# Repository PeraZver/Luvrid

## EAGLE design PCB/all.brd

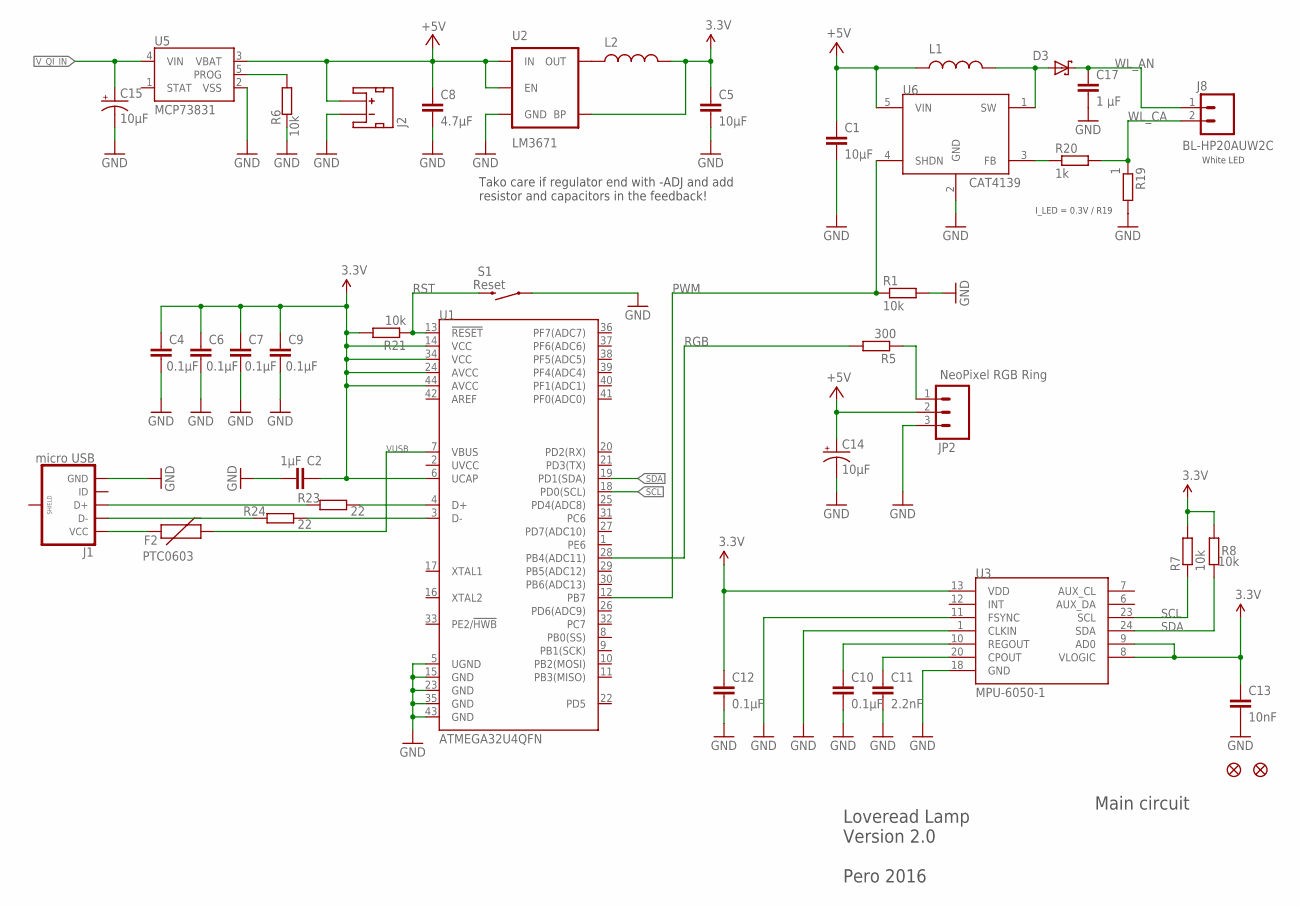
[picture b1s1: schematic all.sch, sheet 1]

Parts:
C1, C5: 10μF; C0603K
C2: 1µF; C0603
C4, C6, C7, C9, C10, C12: 0.1μF; C0603K
C8: 4.7μF; C0603K
C11: 2.2nF; C0603K
C13: 10nF; C0603K
C14, C15: 10μF; EIA3216
C17: 1 μF; C0603K
D3: SMF5.0AT1; SOD123FL
F2: PTC0603; 0603
FD1, FD2: FIDUCIAL1X2; FIDUCIAL-1X2
J1: micro USB; USB-B-MICRO-SMD_V03
J2: LIPO-BATTERY-CONNECTOR; JST-LIPO-CONNECTOR-1.25MM
J8: BL-HP20AUW2C; 1X02
JP2: NeoPixel RGB Ring; 1X03
L1: 22uH; SDR0403
L2: 2.2uH; SDR0403
R1, R6, R7, R8, R21: 10k; R0603
R5: 300; R0603
R19: 1; R0603
R20: 1k; R0603
R23, R24: 22; R0603
S1: Reset; TACTILE-SWITCH-SKSGAAE010
U1: ATMEGA32U4QFN; QFN-44
U2: LM3671; SOT23-5
U3: MPU-6050-1; QFN-24-4MM2
U5: MCP73831; SOT23-5
U6: CAT4139; SOT23-5

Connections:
3.3V: C2.1, C4.1, C5.1, C6.1, C7.1, C9.1, C12.1, C13.1, L2.P$2 (2), R7.2, R8.2, R21.2, U1.6 (UCAP), U1.14 (VCC), U1.24 (AVCC), U1.34 (VCC), U1.44 (AVCC), U2.4 (BP), U3.8 (VLOGIC), U3.9 (AD0), U3.13 (VDD)
+5V: C1.1, C8.1, C14.A (+), J2.P$1 (+), JP2.2, L1.P$1 (1), U2.1 (IN), U2.3 (EN), U5.3 (VBAT), U6.5 (VIN)
GND: C1.2, C2.2, C4.2, C5.2, C6.2, C7.2, C8.2, C9.2, C10.2, C11.2, C12.2, C13.2, C14.C (-), C15.C (-), C17.2, J1.GND, J2.P$2 (-), JP2.3, R1.2, R6.1, R19.2, S1.P$1 (1), S1.P$3 (1), U1.5 (UGND), U1.15 (GND), U1.23 (GND), U1.35 (GND), U1.43 (GND), U2.2 (GND), U3.1 (CLKIN), U3.11 (FSYNC), U3.18 (GND), U5.2 (VSS), U6.2 (GND); also elsewhere on the board
unnamed: C11.1, U3.20 (CPOUT)
unnamed: C10.1, U3.10 (REGOUT)
unnamed: JP2.1, R5.1
unnamed: R6.2, U5.5 (PROG)
unnamed: D3.A, L1.P$2 (2), U6.1 (SW)
unnamed: R20.1, U6.3 (FB)
unnamed: L2.P$1 (1), U2.5 (OUT)
unnamed: F2.1, J1.VBUS (VCC)
unnamed: J1.D+, R23.1
unnamed: J1.D-, R24.1
unnamed: R23.2, U1.4 (D+)
unnamed: R24.2, U1.3 (D-)
PWM: R1.1, U1.12 (PB7), U6.4 (SHDN)
RGB: R5.2, U1.28 (PB4(ADC11))
RST: R21.1, S1.P$2 (2), S1.P$4 (2), U1.13 (!RESET)
SCL: R7.1, U1.18 (PD0(SCL)), U3.23 (SCL)
SDA: R8.1, U1.19 (PD1(SDA)), U3.24 (SDA)
VUSB: F2.2, U1.7 (VBUS)
V_QI_IN: C15.A (+), U5.4 (VIN); also elsewhere on the board
WL_AN: C17.1, D3.C, J8.1
WL_CA: J8.2, R19.1, R20.2

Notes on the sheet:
Loveread Lamp Version 2.0 Pero 2016
Main circuit
I_LED = 0.3V / R19
White LED
Tako care if regulator end with -ADJ and add resistor and capacitors in the feedback!

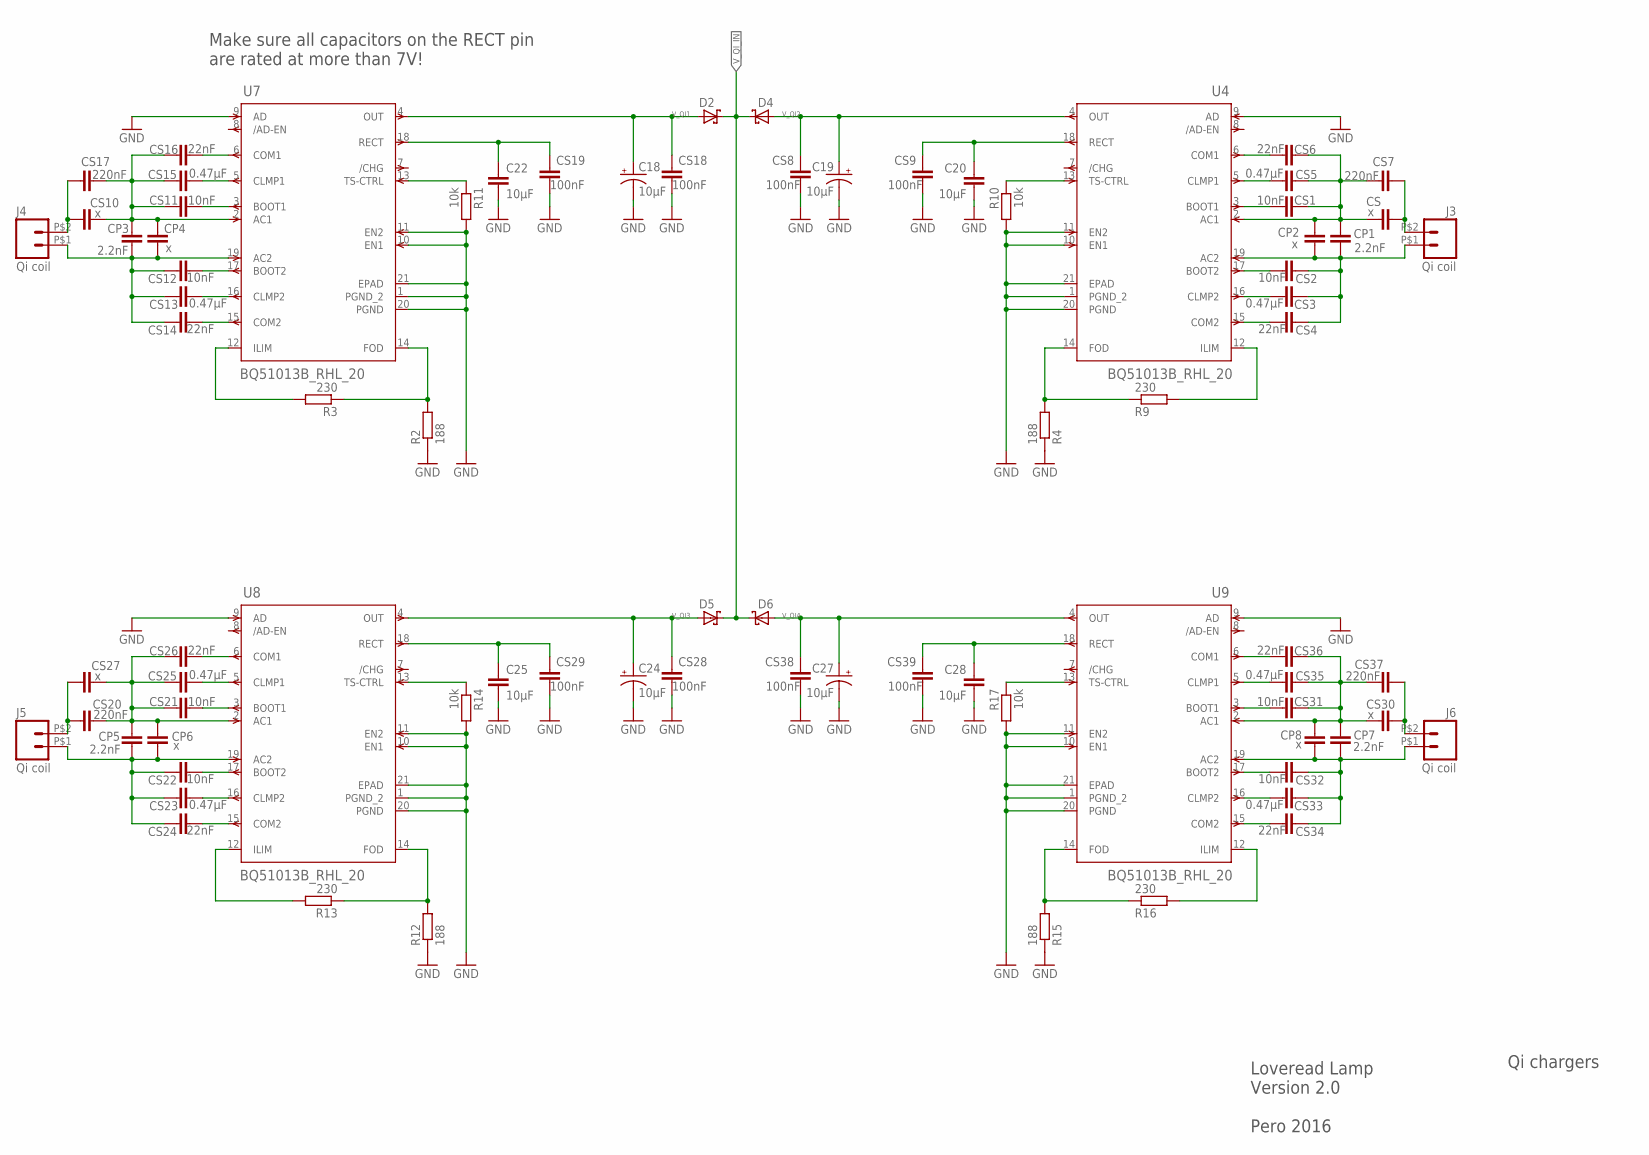
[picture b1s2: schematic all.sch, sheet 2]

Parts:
C18, C19, C24, C27: 10μF; EIA3216
C20, C22, C25, C28: 10μF; C0603K
CP1, CP3, CP5, CP7: 2.2nF; C0603K
CP2, CP4, CP6, CP8: x; C0603K
CS, CS10, CS27, CS30: x; C0603K
CS1, CS2, CS11, CS12, CS21, CS22, CS31, CS32: 10nF; C0603K
CS3, CS5, CS13, CS15, CS23, CS25, CS33, CS35: 0.47μF; C0603K
CS4, CS6, CS14, CS16, CS24, CS26, CS34, CS36: 22nF; C0603K
CS7, CS17, CS20, CS37: 220nF; C0603K
CS8, CS9, CS19, CS28, CS29, CS38, CS39: 100nF; C0603K
CS18: 100nF; C0603
D2, D4, D5, D6: SMF5.0AT1; SOD123FL
J3, J4, J5, J6: Qi coil; 1X02_BIG
R2, R4, R12, R15: 188; R0603
R3, R9, R13, R16: 230; R0603
R10, R11, R14, R17: 10k; R0603
U4, U7, U8, U9: BQ51013B_RHL_20; RHL20_2P05X3P05

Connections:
GND: C18.C (-), C19.C (-), C20.2, C22.2, C24.C (-), C25.2, C27.C (-), C28.2, CS8.2, CS9.2, CS18.2, CS19.2, CS28.2, CS29.2, CS38.2, CS39.2, R2.1, R4.1, R10.2, R11.2, R12.1, R14.2, R15.1, R17.2, U4.1 (PGND_2), U4.9 (AD), U4.10 (EN1), U4.11 (EN2), U4.20 (PGND), U4.21 (EPAD), U7.1 (PGND_2), U7.9 (AD), U7.10 (EN1), U7.11 (EN2), U7.20 (PGND), U7.21 (EPAD), U8.1 (PGND_2), U8.9 (AD), U8.10 (EN1), U8.11 (EN2), U8.20 (PGND), U8.21 (EPAD), U9.1 (PGND_2), U9.9 (AD), U9.10 (EN1), U9.11 (EN2), U9.20 (PGND), U9.21 (EPAD); also elsewhere on the board
unnamed: CS10.1, CS17.1, J4.P$2 (2)
unnamed: CP3.1, CP4.1, CS12.1, CS13.1, CS14.1, J4.P$1 (1), U7.19 (AC2)
unnamed: CP1.2, CP2.2, CS.2, CS1.1, CS5.1, CS6.1, CS7.2, U4.2 (AC1)
unnamed: CS.1, CS7.1, J3.P$2 (2)
unnamed: CP1.1, CP2.1, CS2.1, CS3.1, CS4.1, J3.P$1 (1), U4.19 (AC2)
unnamed: CS1.2, U4.3 (BOOT1)
unnamed: CS2.2, U4.17 (BOOT2)
unnamed: CS3.2, U4.16 (CLMP2)
unnamed: CS11.2, U7.3 (BOOT1)
unnamed: CS4.2, U4.15 (COM2)
unnamed: CS6.2, U4.6 (COM1)
unnamed: CS5.2, U4.5 (CLMP1)
unnamed: CS12.2, U7.17 (BOOT2)
unnamed: C20.1, CS9.1, U4.18 (RECT)
unnamed: R9.2, U4.12 (ILIM)
unnamed: R4.2, R9.1, U4.14 (FOD)
unnamed: R10.1, U4.13 (TS-CTRL)
unnamed: CS13.2, U7.16 (CLMP2)
unnamed: CS14.2, U7.15 (COM2)
unnamed: CS16.2, U7.6 (COM1)
unnamed: CS15.2, U7.5 (CLMP1)
unnamed: CP3.2, CP4.2, CS10.2, CS11.1, CS15.1, CS16.1, CS17.2, U7.2 (AC1)
unnamed: C22.1, CS19.1, U7.18 (RECT)
unnamed: R3.2, U7.12 (ILIM)
unnamed: R2.2, R3.1, U7.14 (FOD)
unnamed: R11.1, U7.13 (TS-CTRL)
unnamed: CS20.1, CS27.1, J5.P$2 (2)
unnamed: CP5.1, CP6.1, CS22.1, CS23.1, CS24.1, J5.P$1 (1), U8.19 (AC2)
unnamed: CS21.2, U8.3 (BOOT1)
unnamed: CS22.2, U8.17 (BOOT2)
unnamed: CS23.2, U8.16 (CLMP2)
unnamed: CS24.2, U8.15 (COM2)
unnamed: CS26.2, U8.6 (COM1)
unnamed: CS25.2, U8.5 (CLMP1)
unnamed: CP5.2, CP6.2, CS20.2, CS21.1, CS25.1, CS26.1, CS27.2, U8.2 (AC1)
unnamed: C25.1, CS29.1, U8.18 (RECT)
unnamed: R13.2, U8.12 (ILIM)
unnamed: R12.2, R13.1, U8.14 (FOD)
unnamed: R14.1, U8.13 (TS-CTRL)
unnamed: CS30.1, CS37.1, J6.P$2 (2)
unnamed: CP7.1, CP8.1, CS32.1, CS33.1, CS34.1, J6.P$1 (1), U9.19 (AC2)
unnamed: CS31.2, U9.3 (BOOT1)
unnamed: CS32.2, U9.17 (BOOT2)
unnamed: CS33.2, U9.16 (CLMP2)
unnamed: CS34.2, U9.15 (COM2)
unnamed: CS36.2, U9.6 (COM1)
unnamed: CS35.2, U9.5 (CLMP1)
unnamed: CP7.2, CP8.2, CS30.2, CS31.1, CS35.1, CS36.1, CS37.2, U9.2 (AC1)
unnamed: C28.1, CS39.1, U9.18 (RECT)
unnamed: R16.2, U9.12 (ILIM)
unnamed: R15.2, R16.1, U9.14 (FOD)
unnamed: R17.1, U9.13 (TS-CTRL)
V_QI1: C18.A (+), CS18.1, D2.A, U7.4 (OUT)
V_QI2: C19.A (+), CS8.1, D4.A, U4.4 (OUT)
V_QI3: C24.A (+), CS28.1, D5.A, U8.4 (OUT)
V_QI4: C27.A (+), CS38.1, D6.A, U9.4 (OUT)
V_QI_IN: D2.C, D4.C, D5.C, D6.C; also elsewhere on the board

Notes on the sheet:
Loveread Lamp Version 2.0 Pero 2016
Qi chargers
Make sure all capacitors on the RECT pin are rated at more than 7V!

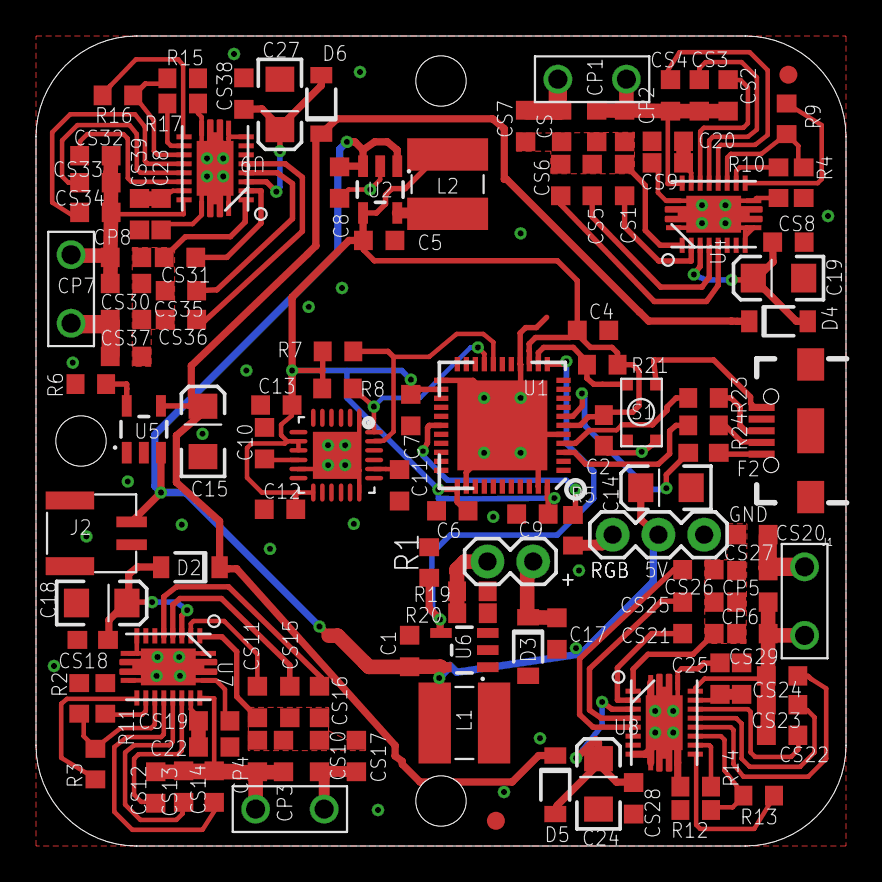
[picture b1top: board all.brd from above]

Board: 2 copper layers, 45.0 x 45.0 mm, 123 parts (0 on the bottom side), 80 nets.

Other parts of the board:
DRILEGEND: DRILEGEND
U$1: Loveread Lamp v2.0; A4L-LOC

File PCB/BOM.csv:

"Qty";"Value";"Device";"Package";"Parts";"Description";"DATASHEETURL";"DESCRIPTION";"DIST";"DIST_ID";"FAMILY_NAME";"GENERIC_PART_NUMBER";"INDUSTRY_STD_PKG_TYPE";"MANUFACTURER";"MANUFACTURER_PART_NUMBER";"PACKAGE_DESIGNATOR";"PIN_COUNT";"PROD_ID";"RS-NUMBER";"SUPPLIER-ID";"VALUE";"VENDOR";
"2";"";"JUMPER-PAD-3-2OF3_NC_BY_TRACE_SMALL";"PAD-JUMPER-3-2OF3_NC_BY_TRACE_YES_SILK_FULL_BOX";"SJ1, SJ2";"";"";"";"";"";"";"";"";"";"";"";"";"";"";"";"";"";
"5";"0.1µF";"C-EUC0603K";"C0603K";"C6, C7, C9, C10, C12";"CAPACITOR, European symbol";"";"";"";"";"";"";"";"";"";"";"";"";"";"";"";"";
"8";"0.47µF";"C-EUC0603K";"C0603K";"CS3, CS5, CS13, CS15, CS23, CS25, CS33, CS35";"CAPACITOR, European symbol";"";"";"";"";"";"";"";"";"";"";"";"";"";"";"";"";
"1";"1";"R-EU_R0603";"R0603";"R19";"RESISTOR, European symbol";"";"";"";"";"";"";"";"";"";"";"";"";"";"";"";"";
"1";"1 µF";"C-EUC0603K";"C0603K";"C17";"CAPACITOR, European symbol";"";"";"";"";"";"";"";"";"";"";"";"";"";"";"";"";
"1";"1.8";"R-EU_R0603";"R0603";"R18";"RESISTOR, European symbol";"";"";"";"";"";"";"";"";"";"";"";"";"";"";"";"";
"1";"100nF";"C-EUC0603";"C0603";"CS18";"CAPACITOR, European symbol";"";"";"";"";"";"";"";"";"";"";"";"";"";"";"";"";
"7";"100nF";"C-EUC0603K";"C0603K";"CS8, CS9, CS19, CS28, CS29, CS38, CS39";"CAPACITOR, European symbol";"";"";"";"";"";"";"";"";"";"";"";"";"";"";"";"";
"8";"10k";"R-EU_R0603";"R0603";"R1, R6, R7, R8, R10, R11, R14, R17";"RESISTOR, European symbol";"";"";"";"";"";"";"";"";"";"";"";"";"";"";"";"";
"9";"10nF";"C-EUC0603K";"C0603K";"C13, CS1, CS2, CS11, CS12, CS21, CS22, CS31, CS32";"CAPACITOR, European symbol";"";"";"";"";"";"";"";"";"";"";"";"";"";"";"";"";
"6";"10µF";"C-EUC0603K";"C0603K";"C1, C5, C20, C22, C25, C28";"CAPACITOR, European symbol";"";"";"";"";"";"";"";"";"";"";"";"";"";"";"";"";
"6";"10µF";"CAP_POL1206";"EIA3216";"C14, C15, C18, C19, C24, C27";"Capacitor Polarized";"";"";"";"";"";"";"";"";"";"";"";"";"";"";"";"";
"4";"188";"R-EU_R0603";"R0603";"R2, R4, R12, R15";"RESISTOR, European symbol";"";"";"";"";"";"";"";"";"";"";"";"";"";"";"";"";
"16";"18pF";"C-EUC0603K";"C0603K";"CP1, CP2, CP3, CP4, CP5, CP6, CP7, CP8, CS, CS7, CS10, CS17, CS20, CS27, CS30, CS37";"CAPACITOR, European symbol";"";"";"";"";"";"";"";"";"";"";"";"";"";"";"";"";
"1";"1k";"R-EU_R0603";"R0603";"R20";"RESISTOR, European symbol";"";"";"";"";"";"";"";"";"";"";"";"";"";"";"";"";
"1";"2.2nF";"C-EUC0603K";"C0603K";"C11";"CAPACITOR, European symbol";"";"";"";"";"";"";"";"";"";"";"";"";"";"";"";"";
"1";"2.2uH";"INDUCTORSDR0403-560KL";"SDR0403";"L2";"Inductors";"";"";"DIGIKEY";"SDR0403-560KLCT-ND";"";"";"";"";"";"";"";"";"";"";"56uH";"";
"8";"22nF";"C-EUC0603K";"C0603K";"CS4, CS6, CS14, CS16, CS24, CS26, CS34, CS36";"CAPACITOR, European symbol";"";"";"";"";"";"";"";"";"";"";"";"";"";"";"";"";
"1";"22uH";"INDUCTORSDR0403-560KL";"SDR0403";"L1";"Inductors";"";"";"DIGIKEY";"SDR0403-560KLCT-ND";"";"";"";"";"";"";"";"";"";"";"56uH";"";
"4";"230";"R-EU_R0603";"R0603";"R3, R9, R13, R16";"RESISTOR, European symbol";"";"";"";"";"";"";"";"";"";"";"";"";"";"";"";"";
"1";"300";"R-EU_R0603";"R0603";"R5";"RESISTOR, European symbol";"";"";"";"";"";"";"";"";"";"";"";"";"";"";"";"";
"1";"4.7µF";"C-EUC0603K";"C0603K";"C8";"CAPACITOR, European symbol";"";"";"";"";"";"";"";"";"";"";"";"";"";"";"";"";
"1";"ATTINY1634MLF20";"ATTINY1634MLF20";"MLF20";"U1";"";"";"";"";"";"";"";"";"";"";"";"";"";"";"";"";"";
"1";"BL-HP20AUW2C";"M02PTH";"1X02";"J8";"Standard 2-pin 0.1" header. Use with";"";"";"";"";"";"";"";"";"";"";"";"";"";"";"";"";
"4";"BQ51013B_RHL_20";"BQ51013B_RHL_20";"RHL20_2P05X3P05";"U4, U7, U8, U9";"";"http://www.ti.com/lit/gpn/BQ51013B";"WPC 1.1 Compatible Fully Integrated Wireless Power Receiver IC";"";"";"Wireless Power - Receiver Solutions";"BQ51013B";"QFN";"Texas Instruments";"bq51013b_rhl_20";"RHL";"20";"";"";"";"";"Texas Instruments";
"1";"CAT4139";"CAT4139";"SOT23-5";"U6";"The CAT4139 is a DC/DC step-up converter that delivers an";"";"";"";"";"";"";"";"On Semiconductor";"";"";"";"";"789-3840";"";"CAT4139";"";
"2";"FIDUCIAL1X2";"FIDUCIAL1X2";"FIDUCIAL-1X2";"FD1, FD2";"Fiducial Alignment Points";"";"";"";"";"";"";"";"";"";"";"";"";"";"";"";"";
"1";"ISP Programmer";"AVR_SPI_PRG_6PTH";"2X3";"J1";"AVR ISP 6 Pin";"";"";"";"";"";"";"";"";"";"";"";"";"";"";"";"";
"1";"LIPO-BATTERY-CONNECTOR";"LIPO-BATTERY-CONNECTOR";"JST-LIPO-CONNECTOR-1.25MM";"J2";"LiPo Battery connector,";"";"";"";"";"";"";"";"JST";"";"";"";"";"752-1790";"SM02B-GHS-TB(LF)(SN)";"";"";
"1";"LM3671";"LM36713.3V";"SOT23-5";"U2";"LM3671/-Q1 2-MHz, 600-mA Step-Down DC-DC Converter";"";"";"";"";"";"";"";"Texas Instruments";"";"";"";"VREG-00822";"537-9547";"";"";"";
"1";"MCP73831";"MCP73831";"SOT23-5";"U5";"Miniature single cell, fully integrated Li-Ion, Li-polymer charge management controller";"";"";"";"";"";"";"";"";"";"";"";"IC-09995";"";"";"";"";
"1";"MPU-6050-1";"MPU-6050-1";"QFN-24-4MM2";"U3";"";"";"";"";"";"";"";"";"";"";"";"";"";"";"";"";"";
"2";"NPN";"TRANSISTOR_NPNSOT23-3";"SOT23-3";"Q1, Q2";"Generic NPN BJT";"";"";"";"";"";"";"";"";"";"";"";"TRANS-08049";"";"";"";"";
"1";"NeoPixel RGB Ring";"M03PTH";"1X03";"JP2";"Header 3";"";"";"";"";"";"";"";"";"";"";"";"";"";"";"";"";
"4";"Qi coil";"M02PTH2";"1X02_BIG";"J3, J4, J5, J6";"Standard 2-pin 0.1" header. Use with";"";"";"";"";"";"";"";"";"";"";"";"";"";"";"";"";
"5";"SMF5.0AT1";"SMF5.0AT1";"SOD123FL";"D2, D3, D4, D5, D6";"200 W Transient Voltage Suppressor";"";"";"";"";"";"";"";"";"";"";"";"";"";"";"";"";
"1";"UART";"M02PTH";"1X02";"J7";"Standard 2-pin 0.1" header. Use with";"";"";"";"";"";"";"";"";"";"";"";"";"";"";"";"";

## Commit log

2016-03-09 First commit of the Loveread Lamp Project.
2016-03-09 Just testing the commits with some stupit comment change
2016-03-09 Still playing with GIT - this time I wanted to see how does it recognize the changes in Eagle files.
2016-03-12 Limit rotation within the range of palm turn.
    Light intensity goes from 20 to 255 as much as you can turn your hand
    simply.
2016-07-17 added gitignore file
2016-07-17 Symmetrical Intensity calculation for both lamps
2016-07-26 added 3D models
2016-07-26 Add 3D model
2016-07-26 remove datasheets
2016-07-31 Adding Qi receiver modules
2016-07-31 Adding Tiny163 4 instead of mega32u4
2016-08-02 Two-sheet schematics, and routing Qi chargers
2016-08-23 Qi chargers routed
2016-08-25 LED driver changed
2016-08-25 Adds buck converter
2016-08-26 rerouted Qi chargers and finished arrangements
2016-08-26 Component placement
2016-08-27 routing finished
2016-08-27 DRC done
2016-08-28 gerber generated
2016-08-28 remove pdf files
2016-08-29 improved spacing, added silkscreen
2016-08-29 fix untracked files
2016-08-30 fabrication output generated
2016-09-01 finished 3D model
2016-11-13 going back to 32u4
2016-11-13 started routing with 32u4
2016-11-15 order complete
2017-02-26 version 3.0 complete release
2017-03-05 modified code to run on 8MHz atmega 32u4
2017-04-19 set system clock to 8 MHz
2017-05-08 no xtal and no transistor LED drivers
2017-09-24 qi coil switch prototype
2017-09-24 rm unnecessary code examples

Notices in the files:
parts and their libraries:
SparkFun-Connectors: Licensing: Creative Commons ShareAlike 4.0 International - https://creativecommons.org/licenses/by-sa/4.0
